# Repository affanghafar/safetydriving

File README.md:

# Driver Drowsiness Detection System using Heart Rate and Postural Changes

## Overview
This project develops a driver drowsiness detection system using physiological and motion data. The system combines heart rate signals and postural changes to classify driver fatigue levels using a Fuzzy Inference System.

---

## System Overview

*Overall functional system diagram for driver drowsiness detection.*

---

## Hardware & Instrumentation

*Prototype device for acquiring ECG and postural data.*

---

## User Interface

*Graphical user interface for monitoring and visualization.*

---

## Data Acquisition

### ECG Signal Acquisition

*Acquisition of heart rate signals using ECG sensor.*

---

### Postural Data Acquisition

*Measurement of head movement and postural changes.*

---

## Hardware Design

*Circuit schematic of the embedded system including ECG sensor and motion sensors.*

## Features

### Physiological Features
- Heart Rate (BPM)

### Postural Features
- Head angle
- Angular velocity
- Nodding duration

---

## Methodology

- Signal acquisition from ECG and motion sensors
- Feature extraction from physiological and postural data
- Classification using **Fuzzy Inference System (FIS)**

---

## Key Findings

- Heart rate tends to decrease during drowsiness
- Postural angle and nodding duration increase
- Angular velocity decreases as fatigue increases

---

## Performance

- Achieved overall accuracy of **87.14%**

---

## Technologies
- Embedded System (STM32)
- Signal Processing
- ECG Sensor
- Accelerometer & Gyroscope
- Fuzzy Logic (FIS)

---

## Project Structure
- `embedded/` – Embedded system code  
- `interface/` – GUI application  
- `hardware/` – PCB and device design  
- `images/` – Diagrams and visualization assets  

---

## Author
Afan Ghafar

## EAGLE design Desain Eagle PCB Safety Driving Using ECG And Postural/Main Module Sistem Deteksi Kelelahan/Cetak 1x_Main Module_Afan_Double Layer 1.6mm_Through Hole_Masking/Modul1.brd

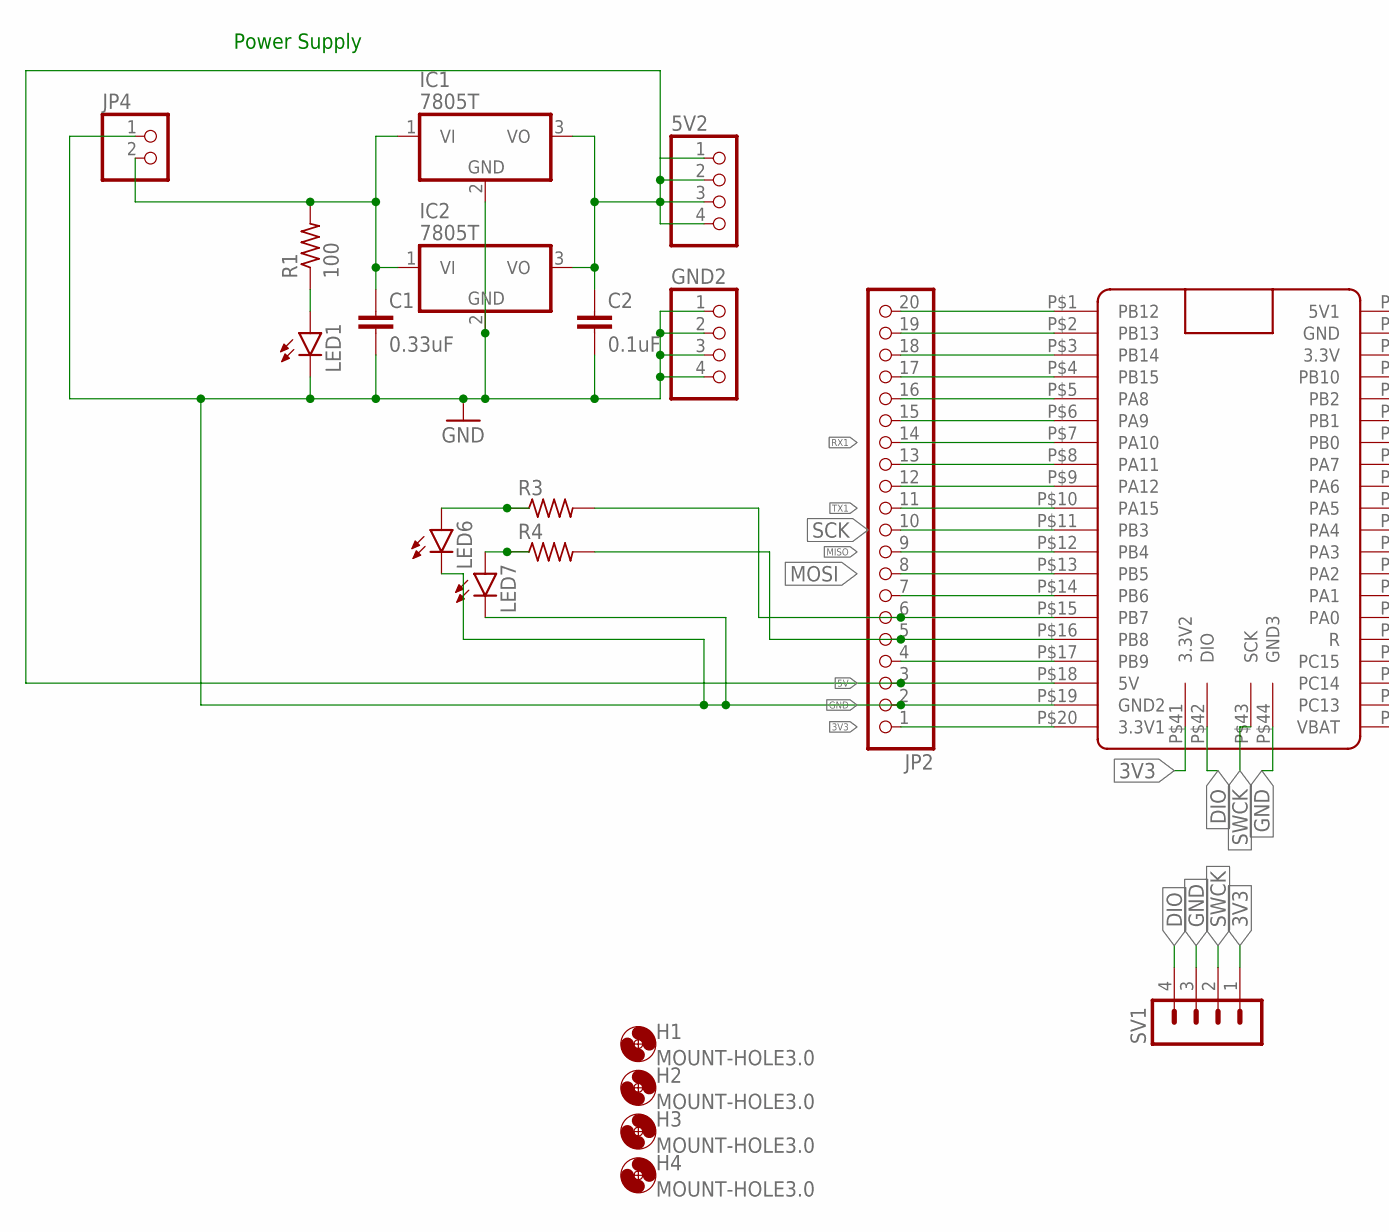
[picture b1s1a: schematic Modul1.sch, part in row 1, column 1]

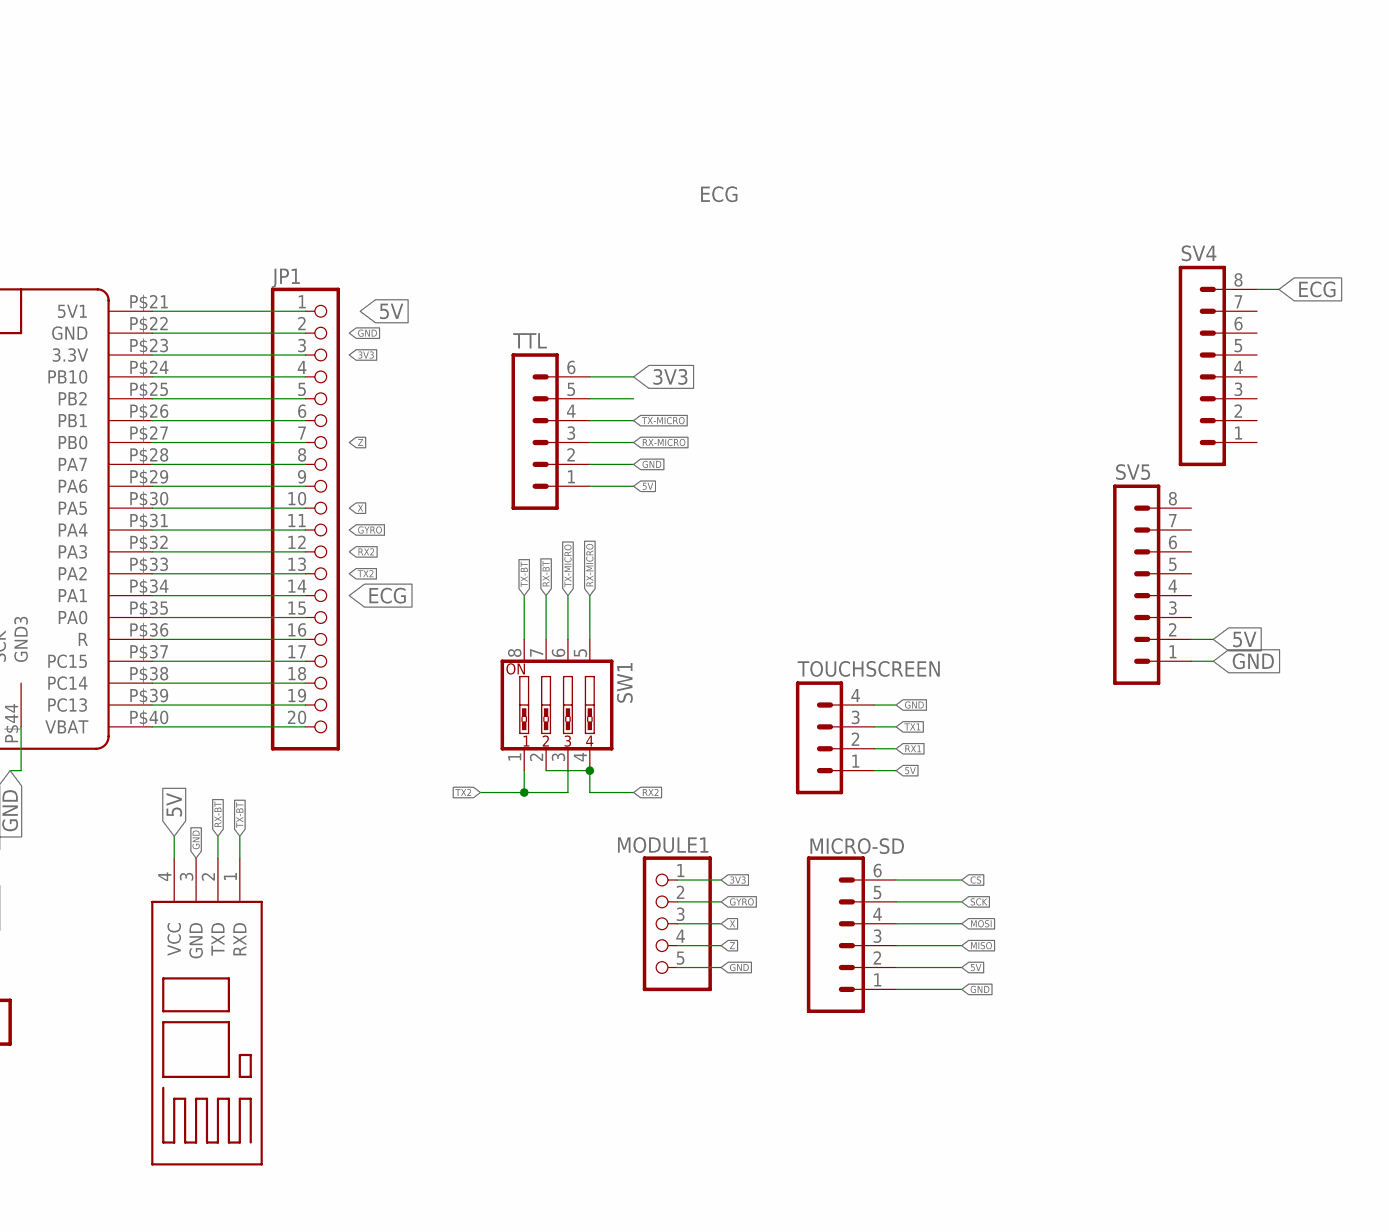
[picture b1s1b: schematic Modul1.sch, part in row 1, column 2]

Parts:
5V2: PINHD-1X4; 1X04
B3: BLUETOOTH
C1: 0.33uF; C025-024X044
C2: 0.1uF; C025-024X044
GND2: PINHD-1X4; 1X04
H1, H2, H3, H4: MOUNT-HOLE3.0; 3,0
IC1, IC2: 7805T; TO220H
JP1, JP2: PINHD-1X20; 1X20
JP4: PINHD-1X2; 1X02
LED1, LED6, LED7: LED5MM
MICRO-SD: CONN_06SILK_FEMALE_PTH; 1X06@1
MODULE1: PINHD-1X5; 1X05
R1: 100; 0204/5
R3, R4: R-US_0204/5; 0204/5
SV1: MA04-1
SV4, SV5: MA08-1
SW1: SW_DIP-4; EDG-04
TOUCHSCREEN: MA04-1
TTL: MA06-1
U$1: BLACKPILL

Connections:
3V3: JP1.3, JP2.1, MODULE1.1, SV1.1, TTL.6, U$1.P$20 (3.3V1), U$1.P$23 (3.3V), U$1.P$41 (3.3V2)
5V: 5V2.1, 5V2.2, 5V2.3, 5V2.4, B3.4 (VCC), C2.1, IC1.3 (VO), IC2.3 (VO), JP1.1, JP2.3, MICRO-SD.2, SV5.2, TOUCHSCREEN.1, TTL.1, U$1.P$18 (5V), U$1.P$21 (5V1)
CS: MICRO-SD.6
DIO: SV1.4, U$1.P$42 (DIO)
ECG: JP1.14, SV4.8, U$1.P$34 (PA1)
GND: B3.3 (GND), C1.2, C2.2, GND2.1, GND2.2, GND2.3, GND2.4, IC1.2 (GND), IC2.2 (GND), JP1.2, JP2.2, JP4.1, LED1.K (C), LED6.K (C), LED7.K (C), MICRO-SD.1, MODULE1.5, SV1.3, SV5.1, TOUCHSCREEN.4, TTL.2, U$1.P$19 (GND2), U$1.P$22 (GND), U$1.P$44 (GND3)
GYRO: JP1.11, MODULE1.2, U$1.P$31 (PA4)
MISO: JP2.9, MICRO-SD.3, U$1.P$12 (PB4)
MOSI: JP2.8, MICRO-SD.4, U$1.P$13 (PB5)
unnamed: JP2.20, U$1.P$1 (PB12)
unnamed: JP2.19, U$1.P$2 (PB13)
unnamed: JP2.18, U$1.P$3 (PB14)
unnamed: C1.1, IC1.1 (VI), IC2.1 (VI), JP4.2, R1.2
unnamed: JP1.8, U$1.P$28 (PA7)
unnamed: JP1.4, U$1.P$24 (PB10)
unnamed: LED1.A, R1.1
unnamed: JP2.12, U$1.P$9 (PA12)
unnamed: JP2.5, R4.2, U$1.P$16 (PB8)
unnamed: LED6.A, R3.1
unnamed: LED7.A, R4.1
unnamed: JP2.7, U$1.P$14 (PB6)
unnamed: JP1.20, U$1.P$40 (VBAT)
unnamed: JP1.19, U$1.P$39 (PC13)
unnamed: JP1.18, U$1.P$38 (PC14)
unnamed: JP1.17, U$1.P$37 (PC15)
unnamed: JP1.16, U$1.P$36 (R)
unnamed: JP1.5, U$1.P$25 (PB2)
unnamed: JP1.6, U$1.P$26 (PB1)
unnamed: JP1.15, U$1.P$35 (PA0)
RX1: JP2.14, TOUCHSCREEN.2, U$1.P$7 (PA10)
RX2: JP1.12, SW1.2, SW1.4, U$1.P$32 (PA3)
RX-BT: B3.2 (TXD), SW1.7
RX-MICRO: SW1.5, TTL.3
SCK: JP2.10, MICRO-SD.5, U$1.P$11 (PB3)
SDA: JP2.4, U$1.P$17 (PB9)
SDIO_CK: JP2.17, U$1.P$4 (PB15)
SDIO_CMD: JP1.9, U$1.P$29 (PA6)
SDIO_D0: JP2.6, R3.2, U$1.P$15 (PB7)
SDIO_D1: JP2.16, U$1.P$5 (PA8)
SDIO_D2: JP2.15, U$1.P$6 (PA9)
SWCK: SV1.2, U$1.P$43 (SCK)
TX1: JP2.11, TOUCHSCREEN.3, U$1.P$10 (PA15)
TX2: JP1.13, SW1.1, SW1.3, U$1.P$33 (PA2)
TX6: JP2.13, U$1.P$8 (PA11)
TX-BT: B3.1 (RXD), SW1.8
TX-MICRO: SW1.6, TTL.4
X: JP1.10, MODULE1.3, U$1.P$30 (PA5)
Z: JP1.7, MODULE1.4, U$1.P$27 (PB0)

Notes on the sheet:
ECG
Power Supply

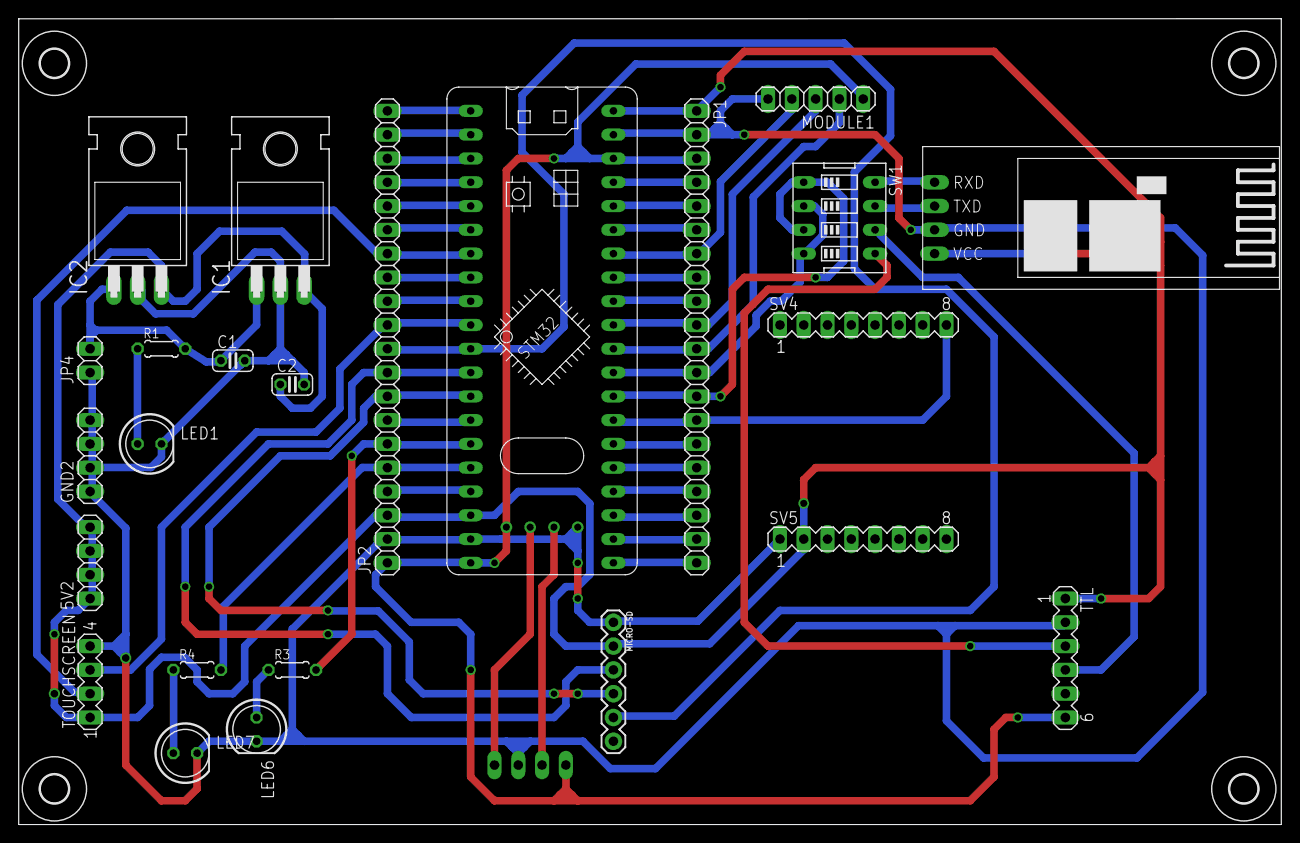
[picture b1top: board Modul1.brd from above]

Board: 2 copper layers, 134.8 x 86.0 mm, 29 parts (1 on the bottom side), 47 nets.

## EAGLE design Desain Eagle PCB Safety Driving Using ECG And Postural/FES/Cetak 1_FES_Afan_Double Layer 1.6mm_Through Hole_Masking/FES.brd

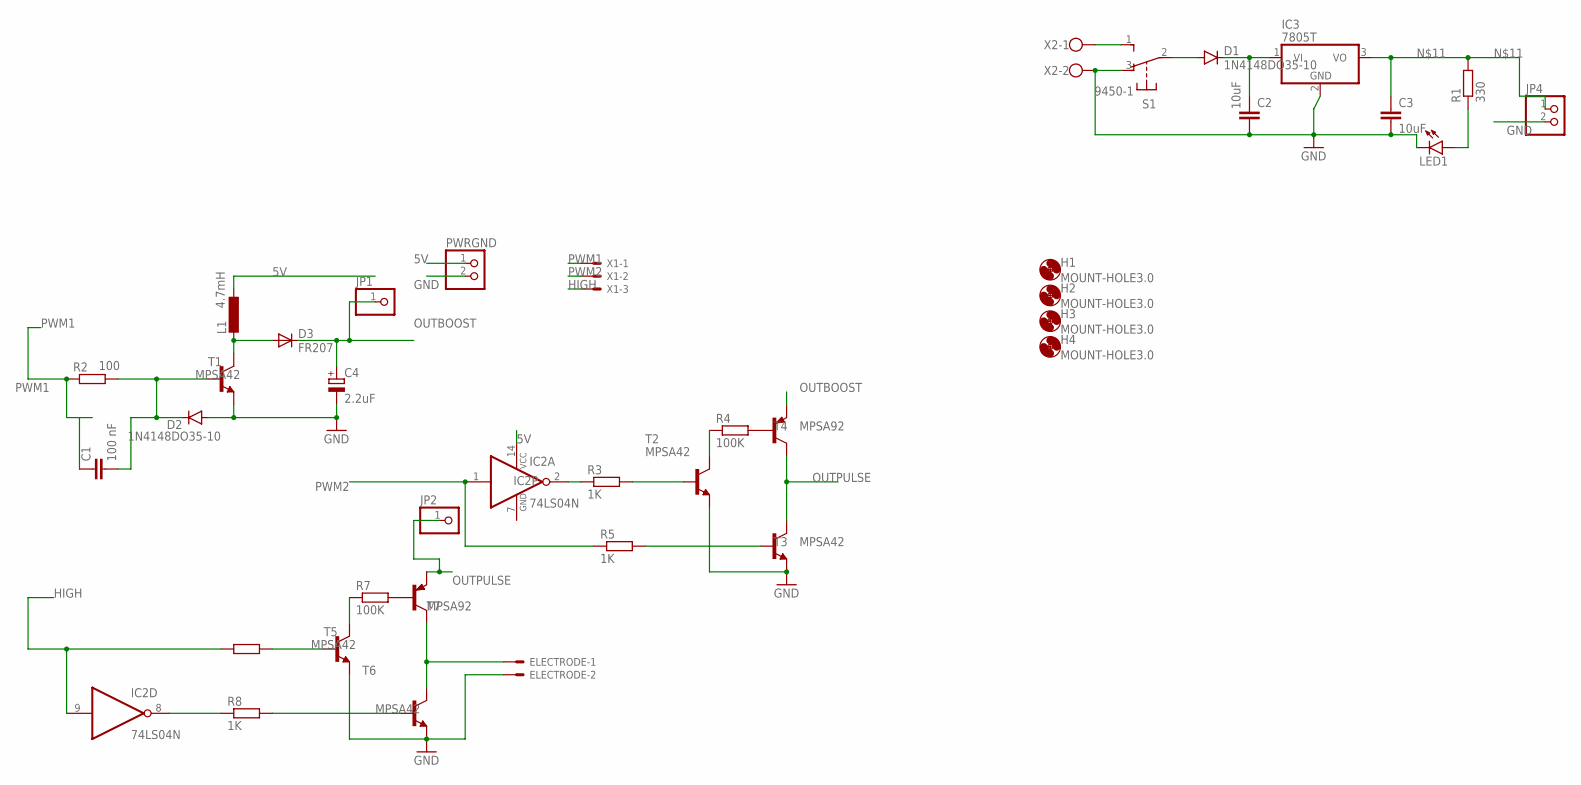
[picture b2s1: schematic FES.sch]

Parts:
C1: 100 nF; C5B2.5
C2, C3: 10uF; C2.5-2
C4: 2.2uF; E5-10,5
D1, D2: 1N4148DO35-10; DO35-10
D3: FR207; DO15-12
ELECTRODE: 22-23-2021
H1, H2, H3, H4: MOUNT-HOLE3.0; 3,0
IC2: 74LS04N; DIL14
IC3: 7805T; TO220H
JP1, JP2: PINHD-1X1; 1X01
JP4: PINHD-1X2; 1X02
L1: 4.7mH; 0207/12
LED1: LED3MM
PWRGND: PINHD-1X2; 1X02
R1: 330; 0207/10
R2: 100; 0207/10
R3, R5, R6, R8: 1K; 0207/10
R4, R7: 100K; 0207/10
S1: 9450-1
T1, T2, T3, T5, T6: MPSA42; TO92-EBC
T4, T7: MPSA92; TO92-EBC
X1: 22-23-2031
X2: W237-102

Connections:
5V: IC2.14 (VCC), L1.1, PWRGND.1
GND: C2.2, C3.2, C4.-, D2.A, ELECTRODE.2, IC2.7 (GND), IC3.2 (GND), JP4.2, LED1.K (C), PWRGND.2, S1.3 (O), T1.E, T2.E, T3.E, T5.E, T6.E, X2.2
HIGH: IC2.9 (I), R6.1, X1.3
unnamed: C1.2, D2.C, R2.2, T1.B
unnamed: S1.1 (S), X2.1
unnamed: D3.A, L1.2, T1.C
unnamed: C2.1, D1.C, IC3.1 (VI)
unnamed: R4.2, T4.B
unnamed: IC2.2 (O), R3.1
unnamed: R3.2, T2.B
unnamed: R4.1, T2.C
unnamed: R7.2, T7.B
unnamed: C3.1, IC3.3 (VO), JP4.1, R1.2
unnamed: IC2.8 (O), R8.1
unnamed: R5.2, T3.B
unnamed: R6.2, T5.B
unnamed: R7.1, T5.C
unnamed: ELECTRODE.1, T6.C, T7.C
unnamed: R8.2, T6.B
unnamed: LED1.A, R1.1
unnamed: D1.A, S1.2
OUTBOOST: C4.+, D3.C, JP1.1, T4.E
OUTPULSE: JP2.1, T3.C, T4.C, T7.E
PWM1: C1.1, R2.1, X1.1
PWM2: IC2.1 (I), R5.1, X1.2

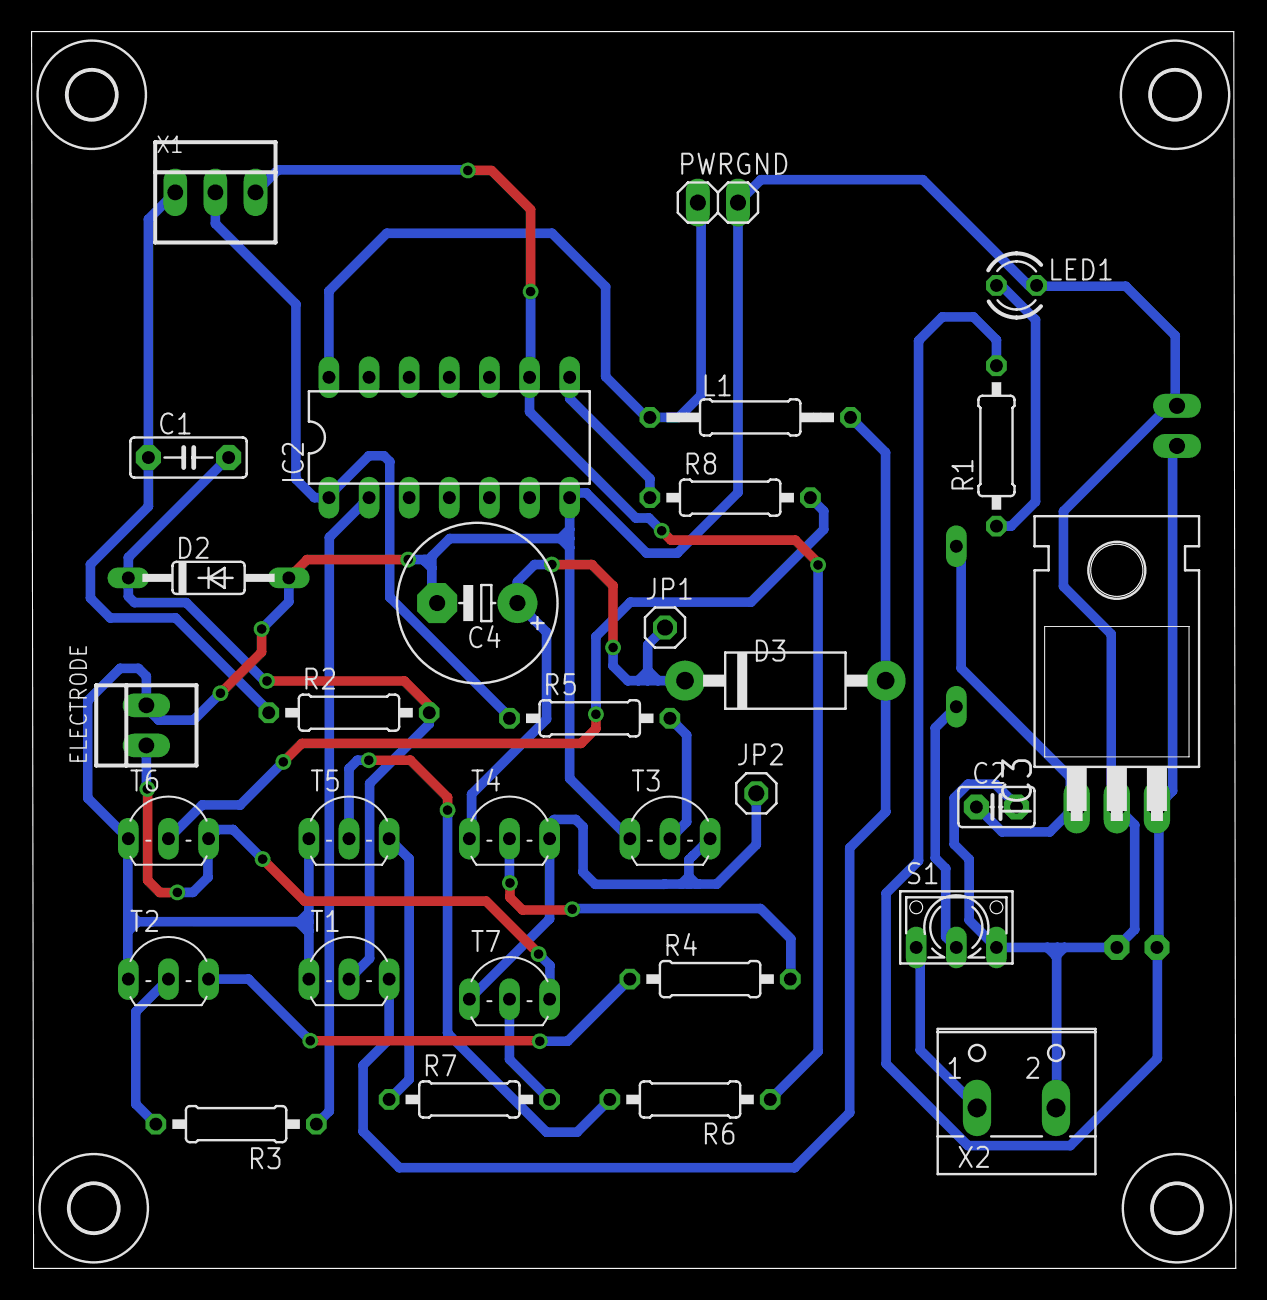
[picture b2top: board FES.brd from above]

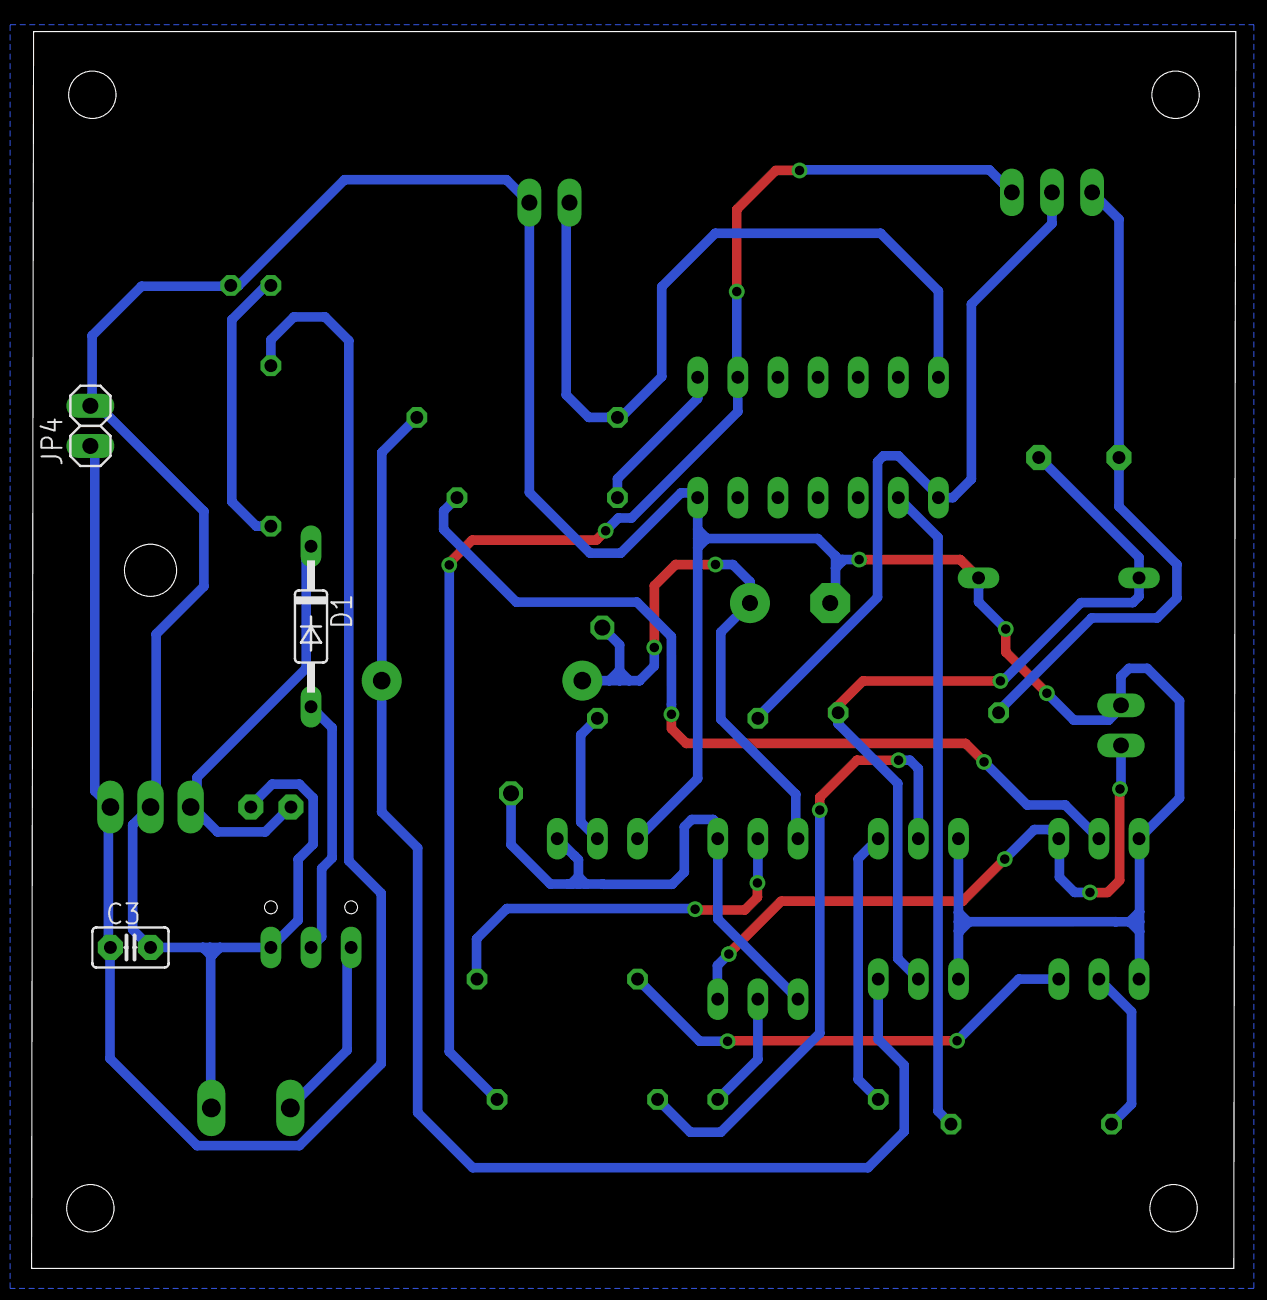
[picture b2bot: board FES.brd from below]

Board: 2 copper layers, 76.2 x 78.3 mm, 38 parts (3 on the bottom side), 25 nets.

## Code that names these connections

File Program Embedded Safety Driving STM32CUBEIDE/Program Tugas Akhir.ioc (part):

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Mcu.Name=STM32F411C(C-E)Ux
Mcu.Package=UFQFPN48
Mcu.UserName=STM32F411CEUx
PA1.Signal=ADCx_IN1
PA10.Mode=Asynchronous
PA10.Signal=USART1_RX
PA11.Mode=Device_Only
PA11.Signal=USB_OTG_FS_DM
PA12.Mode=Device_Only
PA12.Signal=USB_OTG_FS_DP
PA13.Mode=Serial_Wire
PA13.Signal=SYS_JTMS-SWDIO
PA14.Mode=Serial_Wire
PA14.Signal=SYS_JTCK-SWCLK
PA15.Mode=Asynchronous
PA15.Signal=USART1_TX
PA2.Mode=Asynchronous
PA2.Signal=USART2_TX
PA3.Mode=Asynchronous
PA3.Signal=USART2_RX
PA4.Signal=ADCx_IN4
PA5.Signal=ADCx_IN5
PA8.Signal=S_TIM1_CH1
PB0.Signal=ADCx_IN8
PB15.Signal=GPIO_Output
PB3.Mode=Full_Duplex_Master
PB3.Signal=SPI1_SCK
PB4.Mode=Full_Duplex_Master
PB4.Signal=SPI1_MISO
PB5.Mode=Full_Duplex_Master
PB5.Signal=SPI1_MOSI
PB7.Signal=S_TIM4_CH2
PC13-ANTI_TAMP.Signal=GPIO_Output
PH0\ -\ OSC_IN.Mode=HSE-External-Oscillator
PH0\ -\ OSC_IN.Signal=RCC_OSC_IN
PH1\ -\ OSC_OUT.Mode=HSE-External-Oscillator
PH1\ -\ OSC_OUT.Signal=RCC_OSC_OUT
RCC.HSE_VALUE=25000000
RCC.SYSCLKFreq_VALUE=72000000
RCC.SYSCLKSource=RCC_SYSCLKSOURCE_PLLCLK
board=custom

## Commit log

2023-08-31 Nextion
2023-08-31 Interface Safety Driving Delphi7
2023-08-31 /Program Embedded Safety Driving STM32CUBEIDE
2023-08-31 Eagle PCB Safety Driving Using ECG And Postural

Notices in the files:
parts and their libraries:
SparkFun-Connectors: Licensing: Creative Commons ShareAlike 4.0 International - https://creativecommons.org/licenses/by-sa/4.0
